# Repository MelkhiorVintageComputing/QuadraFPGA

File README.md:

# A FPGA on a Quadra PDS card...

## Goal

The goal of this repository is to be able to interface a modern (2023 era) [FPGA](https://en.wikipedia.org/wiki/Field-programmable_gate_array) with a [Macintosh Quadra](https://en.wikipedia.org/wiki/Macintosh_Quadra) using its PDS (Processor Direct Slot) connector. The PDS is basically just a physical connector to the MC68040 memory bus.

So unless you're a retrocomputing enthusiast with such a machine, this is useless. If you are such an enthusiast, then maybe the ability to connect a modern LCD monitor using a digital interface to an old Macintosh might be of interest to you.

This project was 'spun off' the [NuBusFPGA](https://github.com/rdolbeau/NuBusFPGA) and [IIsiFPGA](https://github.com/rdolbeau/IIsiFPGA), similar project for the NuBus used in several models of Macintosh of the era and the PDS in the Macintosh IIsi. NuBusFPGA itself is a spin-off of the [SBusFPGA](https://github.com/rdolbeau/SBusFPGA), a similar project for the SBus used in Sun's SPARCstation.

## Current status

The HDMI (Highly Desirable Macintosh Interface) is working, with both video (single-hardware-res, multi-depth, windowboxed lower res) & audio working. More details are available in the readme of the NuBusFPGA repository.

## Known issue(s)

* The Snoop Control signals (SC0 and SC1) aren't connected to the FPGA. They must be driven low ("Inhibit Snooping", Table 4-1 in the 040UM) by alternate bus master. This prevent the QuadraFPGA to be a bus master, as those signals are pulled high on the motherboard.

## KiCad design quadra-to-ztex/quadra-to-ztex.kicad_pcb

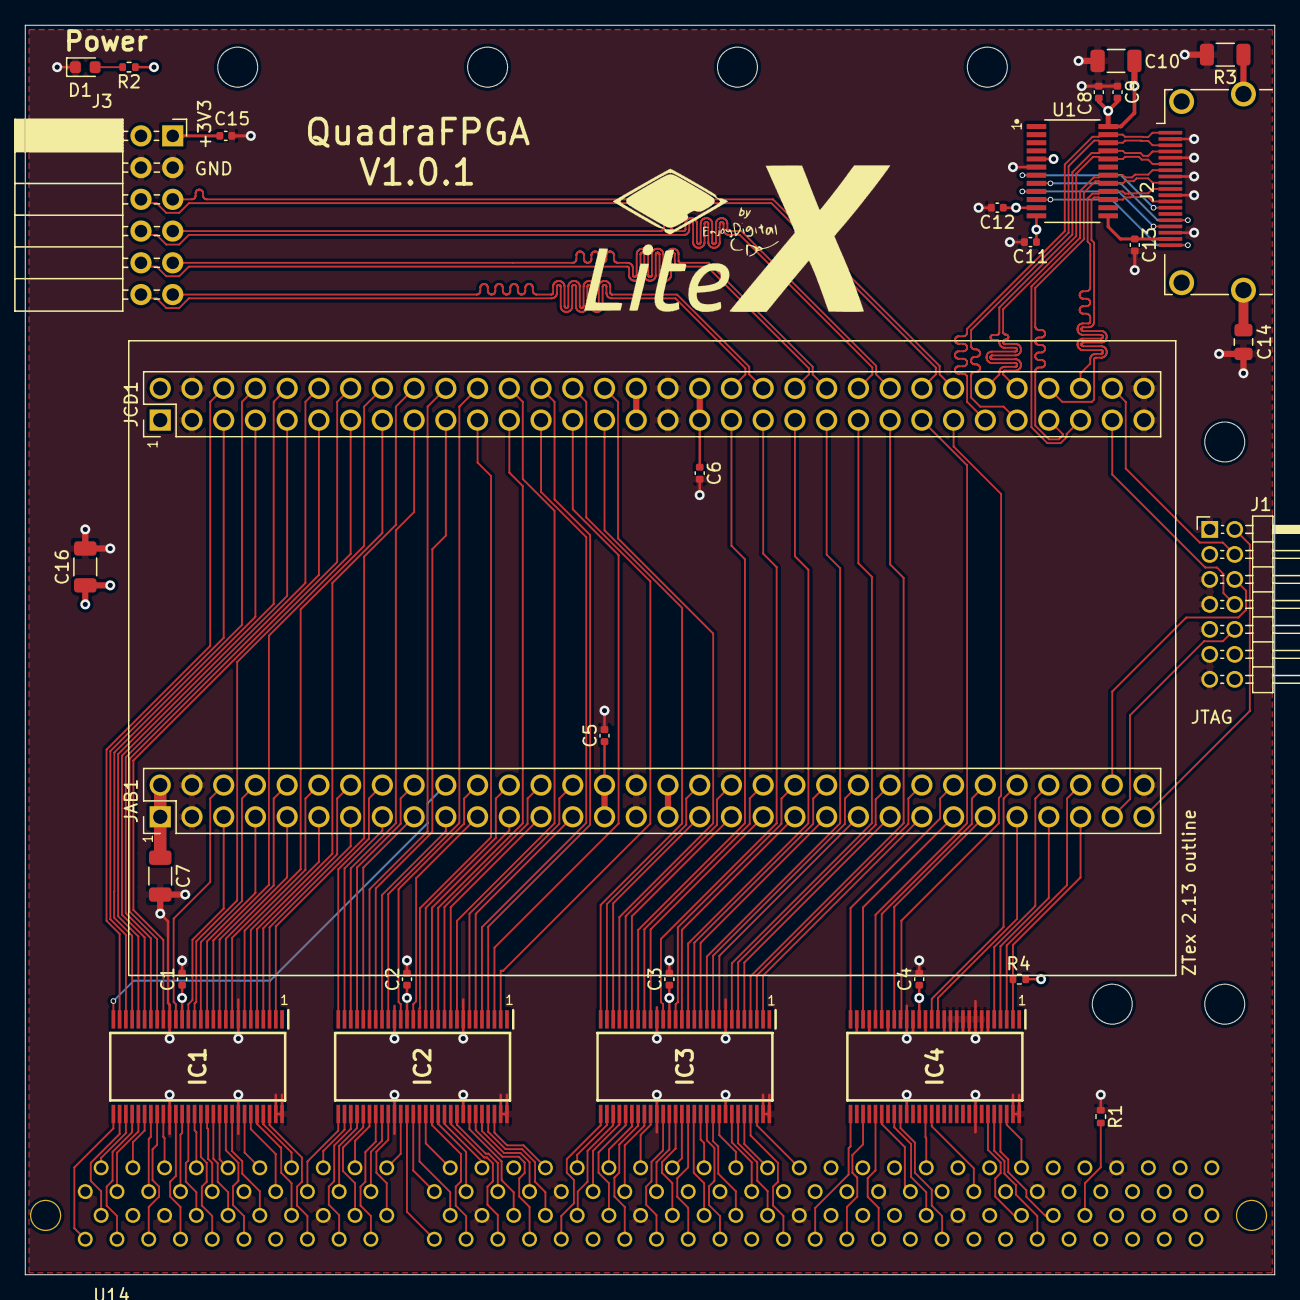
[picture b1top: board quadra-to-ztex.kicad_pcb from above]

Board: 4 copper layers, 100.0 x 100.0 mm, 33 parts (0 on the bottom side), 200 nets.

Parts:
C1, C2, C3, C4, C5, C6, C8, C11, C12, C13, C15: 100nF; C_0402_1005Metric
C7, C16: 47uF 10V+; C_1206_3216Metric
C9: 10nF; C_0402_1005Metric
C10: 47uF 10V 1206; C_1206_3216Metric
C14: 10nF 1kV 0805; C_0805_2012Metric
D1: RED LED 0603; LED_0603_1608Metric
GRAPHIC1: LogoLitex; litex_logo
IC1, IC2, IC3, IC4: 74CB3T16211DGGR; SOP50P810X120-56N
J1: Conn_02x07_Odd_Even; PinHeader_2x07_P2.00mm_Horizontal_For_SeeedStudio
J2: 10029449-111RLF (HDMI A); HDMI_A_Amphenol_10029449-111
J3: A2541HWR-2x6P (Pmod 2x6 F R); PinSocket_2x06_P2.54mm_Horizontal
JAB1: ZTEX_AB-ztex_AB; PinHeader_2x32_P2.54mm_Vertical_For_SeeedStudio
JCD1: ZTEX_CD-ztex_CD; PinHeader_2x32_P2.54mm_Vertical_For_SeeedStudio
R1: 0; R_0402_1005Metric
R2: 680; R_0402_1005Metric
R3: 1M 500V 1206; R_1206_3216Metric
R4: 10k; R_0402_1005Metric
U1: TPD12S016PWR; SOP65P640X120-24N
U14: 8807-140-170LH

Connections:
+3V3: C1.1, C2.1, C3.1, C4.1, C5.1, C6.1, C8.1, C9.1, C10.1, C11.1, C15.1, C16.1, IC1.17, IC2.17, IC3.17, IC4.17, J3.1, J3.2, JAB1.29, JAB1.30, JAB1.33, JAB1.34, JCD1.31, JCD1.32, JCD1.35, JCD1.36, R2.1, R4.1, U1.5, U1.12, U1.24
+5V: C7.1, C12.1, JAB1.1, JAB1.2, U1.11, U14.26, U14.37, U14.56, U14.70, U14.74, U14.83, U14.101, U14.111, U14.121, U14.131, U14.140
/B2B/JTAG_VIO: J1.2, JAB1.63
/hdmi/HDMI_5V: C13.1, J2.18, U1.13
/hdmi/cec_b: J2.13, U1.7
/hdmi/hpd_b: J2.19, U1.10
/hdmi/scl_b: J2.15, U1.8
/hdmi/sda_b: J2.16, U1.9
A0: IC1.30, U14.72
A0_3V3: IC1.27, JCD1.6
A1: IC1.31, U14.2
A1_3V3: IC1.26, JCD1.5
A2: IC1.32, U14.73
A2_3V3: IC1.25, JCD1.8
A3: IC1.33, U14.3
A3_3V3: IC1.24, JCD1.7
A4: IC1.34, U14.4
A4_3V3: IC1.23, JCD1.10
A5: IC1.36, U14.75
A5_3V3: IC1.21, JCD1.12
A6: IC1.35, U14.5
A6_3V3: IC1.22, JCD1.9
A7: IC1.37, U14.6
A7_3V3: IC1.20, JCD1.11
A8: IC1.39, U14.77
A8_3V3: IC1.18, JAB1.6
A9: IC1.40, U14.7
A9_3V3: IC1.16, JAB1.5
A10: IC1.41, U14.78
A10_3V3: IC1.15, JCD1.14
A11: IC1.42, U14.8
A11_3V3: IC1.14, JAB1.8
A12: IC1.43, U14.79
A12_3V3: IC1.13, JAB1.7
A13: IC1.44, U14.9
A13_3V3: IC1.12, JCD1.13
A14: IC1.45, U14.80
A14_3V3: IC1.11, JAB1.10
A15: IC1.46, U14.10
A15_3V3: IC1.10, JAB1.9
A16: IC1.47, U14.81
A16_3V3: IC1.9, JCD1.16
A17: IC1.48, U14.82
A17_3V3: IC1.7, JAB1.12
A18: IC1.50, U14.12
A18_3V3: IC1.6, JAB1.11
A19: IC1.51, U14.13
A19_3V3: IC1.5, JCD1.15
A20: IC1.52, U14.84
A20_3V3: IC1.4, JAB1.14
A21: IC1.53, U14.14
A21_3V3: IC1.3, JAB1.13
A22: IC1.54, U14.85
A22_3V3: IC1.2, JCD1.18
A23: IC2.29, U14.15
A23_3V3: IC2.28, JAB1.16
A24: IC2.30, U14.16
A24_3V3: IC2.27, JAB1.15
A25: IC2.31, U14.87
A25_3V3: IC2.26, JCD1.17
A26: IC2.32, U14.17
A26_3V3: IC2.25, JAB1.18
A27: IC2.33, U14.88
A27_3V3: IC2.24, JAB1.17
A28: IC2.35, U14.89
A28_3V3: IC2.22, JCD1.19
A29: IC2.34, U14.18
A29_3V3: IC2.23, JCD1.20
A30: IC2.37, U14.90
A30_3V3: IC2.20, JCD1.22
A31: IC2.36, U14.19
A31_3V3: IC2.21, JAB1.19
AUX_CPUCLK: IC1.29, U14.71
AUX_CPUCLK_3V3: IC1.28, JAB1.20
D0: IC3.46, U14.109
D0_3V3: IC3.10, JAB1.46
D1: IC3.45, U14.38
D1_3V3: IC3.11, JCD1.43
D2: IC3.44, U14.108
D2_3V3: IC3.12, JAB1.43
D3: IC3.43, U14.107
D3_3V3: IC3.13, JAB1.44
D4: IC3.42, U14.36
D4_3V3: IC3.14, JCD1.41
D5: IC3.41, U14.106
D5_3V3: IC3.15, JAB1.41
D6: IC3.40, U14.35
D6_3V3: IC3.16, JAB1.42
D7: IC3.39, U14.105
D7_3V3: IC3.18, JCD1.39
D8: IC3.37, U14.34
D8_3V3: IC3.20, JAB1.39
D9: IC3.36, U14.33
D9_3V3: IC3.21, JAB1.40
D10: IC3.35, U14.103
D10_3V3: IC3.22, JCD1.37
D11: IC3.34, U14.32
D11_3V3: IC3.23, JAB1.37
D12: IC3.33, U14.102
D12_3V3: IC3.24, JAB1.38
D13: IC3.32, U14.31
D13_3V3: IC3.25, JCD1.30
D14: IC3.30, U14.30
D14_3V3: IC3.27, JAB1.36
D15: IC3.31, U14.100
D15_3V3: IC3.26, JAB1.35
D16: IC3.29, U14.99
D16_3V3: IC3.28, JCD1.29
D17: IC2.54, U14.28
D17_3V3: IC2.2, JCD1.28
D18: IC2.53, U14.98
D18_3V3: IC2.3, JCD1.27
D19: IC2.52, U14.27
D19_3V3: IC2.4, JCD1.26
D20: IC2.51, U14.97
D20_3V3: IC2.5, JCD1.25
D21: IC2.50, U14.96
D21_3V3: IC2.6, JAB1.27
D22: IC2.48, U14.25
D22_3V3: IC2.7, JAB1.28
D23: IC2.47, U14.95
D23_3V3: IC2.9, JCD1.24
D24: IC2.46, U14.24
D24_3V3: IC2.10, JAB1.25
D25: IC2.45, U14.23
D25_3V3: IC2.11, JAB1.26
D26: IC2.44, U14.93
D26_3V3: IC2.12, JCD1.23
D27: IC2.43, U14.22
D27_3V3: IC2.13, JAB1.23
D28: IC2.42, U14.92
D28_3V3: IC2.14, JAB1.24
D29: IC2.41, U14.21
D29_3V3: IC2.15, JCD1.21
D30: IC2.40, U14.91
D30_3V3: IC2.16, JAB1.21
D31: IC2.39, U14.20
D31_3V3: IC2.18, JAB1.22
FPGA_JTAG_TCK: J1.6, JAB1.62
FPGA_JTAG_TDI: J1.10, JAB1.61
FPGA_JTAG_TDO: J1.8, JCD1.61
FPGA_JTAG_TMS: J1.4, JCD1.62
GND: C1.2, C2.2, C3.2, C4.2, C5.2, C6.2, C7.2, C8.2, C9.2, C10.2, C11.2, C12.2, C13.2, C14.2, C15.2, C16.2, D1.1, IC1.8, IC1.19, IC1.38, IC1.49, IC1.55, IC1.56, IC2.8, IC2.19, IC2.38, IC2.49, IC2.55, IC2.56, IC3.8, IC3.19, IC3.38, IC3.49, IC3.55, IC3.56, IC4.6, IC4.7, IC4.8, IC4.9, IC4.10, IC4.11, IC4.12, IC4.13, IC4.16, IC4.18, IC4.19, IC4.22, IC4.25, IC4.27, IC4.38, IC4.49, IC4.55, IC4.56, J1.1, J1.3, J1.5, J1.7, J1.9, J1.11, J1.13, J2.2, J2.5, J2.8, J2.11, J2.17, J3.3, J3.4, JAB1.3, JAB1.4, JAB1.31, JAB1.32, JAB1.64, JCD1.3, JCD1.4, JCD1.33, JCD1.34, JCD1.63, JCD1.64, R1.1, R3.2, U1.6, U14.1, U14.11, U14.29, U14.39, U14.49, U14.59, U14.64, U14.76, U14.86, U14.94, U14.104, U14.114, U14.124
HDMI_CLK+: J2.10, JCD1.60, U1.16
HDMI_CLK-: J2.12, JCD1.58, U1.15
HDMI_D0+: J2.7, JCD1.59, U1.18
HDMI_D0-: J2.9, JCD1.57, U1.17
HDMI_D1+: J2.4, JCD1.54, U1.21
HDMI_D1-: J2.6, JCD1.56, U1.20
HDMI_D2+: J2.1, JCD1.53, U1.23
HDMI_D2-: J2.3, JCD1.55, U1.22
unnamed: D1.2, R2.2
PMOD-56+: J3.6, JCD1.50
PMOD-56-: J3.5, JCD1.52
PMOD-78+: J3.8, JCD1.46
PMOD-78-: J3.7, JCD1.48
PMOD-910+: J3.10, JCD1.42
PMOD-910-: J3.9, JCD1.44
PMOD-1112+: J3.12, JCD1.38
PMOD-1112-: J3.11, JCD1.40
SHIELD: C14.1, J2.SH, R3.1
SIZ0: IC3.47, U14.110
SIZ0_3V3: IC3.9, JAB1.45
SIZ1: IC3.48, U14.40
SIZ1_3V3: IC3.7, JCD1.45
TM0: IC4.51, U14.128
TM0_3V3: IC4.5, JAB1.58
TM1: IC4.52, U14.129
TM1_3V3: IC4.4, JAB1.57
TM2: IC4.53, U14.130
TM2_3V3: IC4.3, JAB1.60
TT0: IC4.36, U14.122
TT0_3V3: IC4.21, JAB1.53
TT1: IC4.37, U14.123
TT1_3V3: IC4.20, JCD1.51
~BB: IC4.41, U14.52
~BB_3V3: IC4.15, JAB1.56
~BG_40SLOT: IC4.33, U14.119
~BG_40SLOT_3V3: IC4.24, JCD1.49
~BR_40SLOT: IC4.34, U14.51
~BR_40SLOT_3V3: IC4.23, JAB1.54
~MI: IC4.31, U14.117
~MI_3V3: IC4.26, JAB1.51
~NMRQ6: IC4.54, U14.58
~NMRQ6_3V3: IC4.2, JAB1.59, R4.2
~PDS_SLOT_E_EN: R1.2, U14.132
~RSTQ: IC4.42, U14.55
~RSTQ_3V3: IC4.14, JAB1.55
~RW: IC3.50, U14.41
~RW_3V3: IC3.6, JAB1.48
~TA: IC3.53, U14.113
~TA_3V3: IC3.3, JAB1.50
~TBI: IC3.51, U14.112
~TBI_3V3: IC3.5, JAB1.47
~TEA: IC3.54, U14.44
~TEA_3V3: IC3.2, JAB1.49
~TIP_CPU: IC3.52, U14.42
~TIP_CPU_3V3: IC3.4, JCD1.47
~TS: IC4.29, U14.115
~TS_3V3: IC4.28, JAB1.52

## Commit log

2023-09-02 early draft
2023-09-02 thinking about 68040 FSM
2023-09-09 length tuning
2023-09-16 license
2023-09-16 remove memreset, add busmastering (?)
2023-09-16 minor fixes
2023-09-17 upd gen files
2023-09-17 prelims
2023-09-17 rewire to avoid p/n conflicts
2023-09-17 more prelims, rewiring
2023-09-19 fix lengths
2023-09-20 logo
2023-09-23 oups A5
2023-10-02 oups wrong pin
2023-10-08 regen
2023-10-21 R1 must be 0 ohm (there's a pull-up on the motherboard and it's stronger)
2023-10-22 prelim bring-up
2023-10-22 v1.0.1
2023-10-29 burst, though slowly as I can't get the two FIFOs mechanism to work
2023-10-29 various attempts at improving burst write
2023-11-01 more burst, weird bug with SyncFIFO for burst...
2023-11-01 fb mem burst, other tests that are weird (why isn't superslot working???)
2023-11-02 change/fix FB mem burst write to go through a FIFO and ddicated port
2023-11-11 fix A18 <-> A19 (gateware)
2023-11-11 fix A18 <-> A19 (hardware)
2023-11-11 drop unused/untested stuff for now, comments
2023-11-11 readme
2023-11-18 move some of board platform stuff to common
2023-11-18 stuff to common
2023-12-02 add ref
2024-01-02 make goblin alt phy a build option, for easier support of non-Full HD resolution
2024-02-11 update reference to fix LUT bug
2024-02-17 catch-up for progammable clock
2024-02-23 drop moved file
2024-02-24 updat e REF
2024-05-18 board-based name
2025-09-07 typo in comment
2025-09-07 no DMA :-(
